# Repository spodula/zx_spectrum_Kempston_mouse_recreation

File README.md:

# zx_spectrum_Kempston_mouse_recreation
This is a copy of the classic Kempston mouse interface re-designed to use Amiga mice.
it uses all the same components, just pinout of the mouse connector differs from the classic kempston mouse.
(So in the unlikely event you have an original kempston mouse, DO NOT plug it in)
I personally use an amiga Mouse adapter I got from Ebay with an old Dell Optical mouse. This seems to work fine. 

Gerbers files are complete, and you should just be able to zip them up and send them straight to your PCB manafacturer of your choice. 

All of this was done from the Schematics available at: 
Kio at https://k1.spdns.de/Vintage/Sinclair/82/Peripherals/Mouse%20Interfaces/Kempston%20Mouse%20Interface/
My additions are:
* support for 3 button mice
* Re-arrange pinout so its compatable with the Amiga mouse. 

BUGS!
-----
Minor bug, C1 should be next to C2, and C8 should be where C1 is for decoupling!
Fortunately, as the board is overly decoupled anyway (And frankly, its doubtful if U2 needs decoupling, as its only changes its logic states a few tens of times a second at most), this isnt really an issue, HOWEVER Do make sure you dont put a 100nf as C1. This could cause bad reads from the mouse. 

Parts required: 
---------------
* 74LS191 x4
* 74LS257 x2
* 74LS138
* 74LS00
* 74LS125
* 10nf capacitor x2
* 100nf capacitors x9
* PCB mount DB9 connector.
* Edge connector x1 (If required)

Note, the jumpers J2,3,4,5 are there because i wasnt sure of the X1/X2 Y1/Y2 order. 
Now i know, you can just jumper the squared pins off (technically Pins 2/3), so the next version probably wont have them. 
(look at the terrible photos in the folder)

No licence on this board, use it, manafacture it, sell it, fart in its general direction, have fun with it..
If you do modify it, be sure to credit Kio at the above URL.

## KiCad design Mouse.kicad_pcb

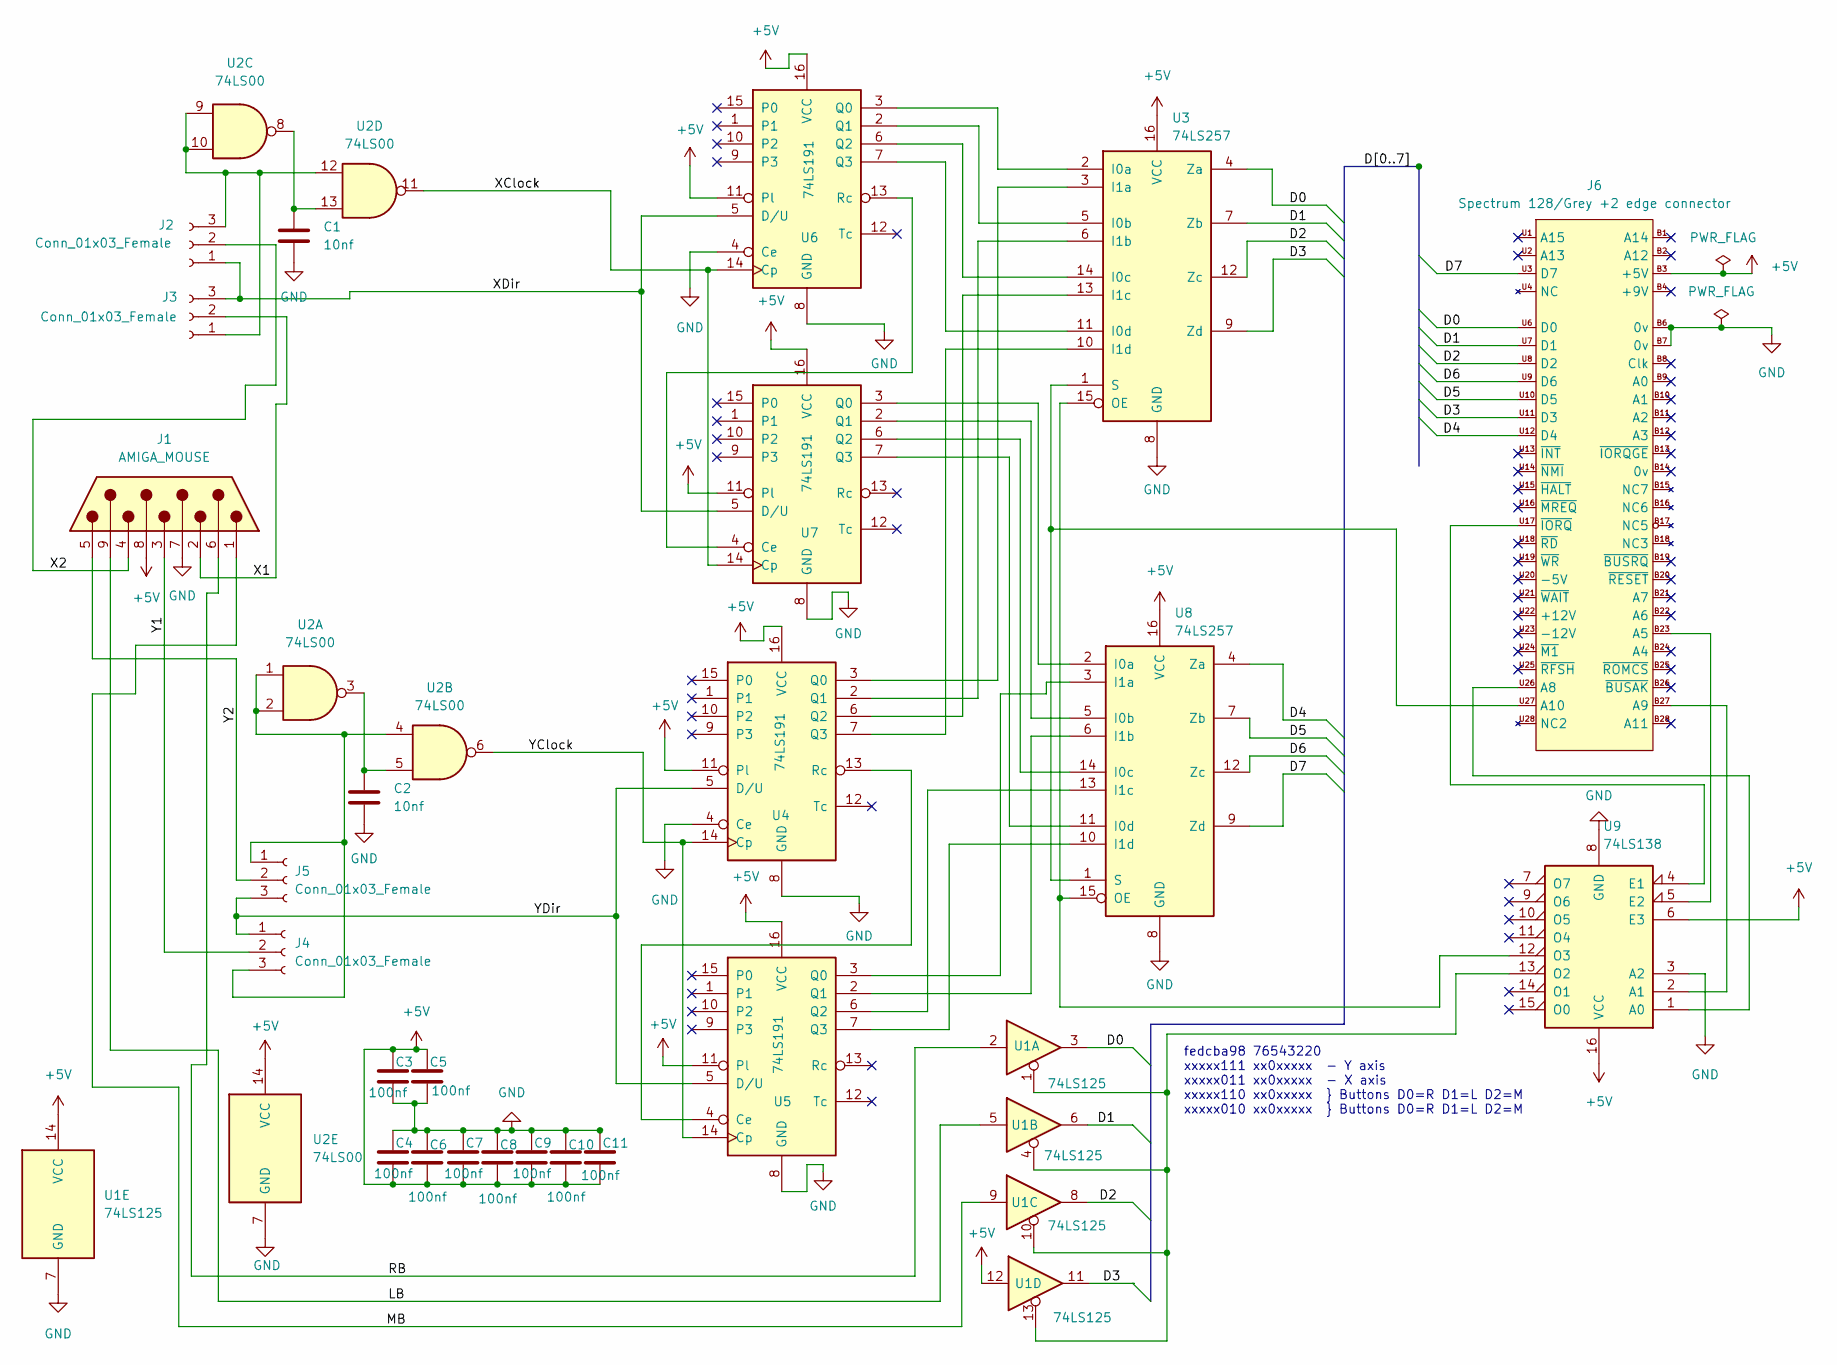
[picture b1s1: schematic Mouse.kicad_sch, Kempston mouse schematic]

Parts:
C1, C2: 10nf; C_Disc_D3.0mm_W1.6mm_P2.50mm
C3, C4, C5, C6, C7, C8, C9, C10, C11: 100nf; C_Disc_D3.0mm_W1.6mm_P2.50mm
J1: AMIGA_MOUSE; DSUB-9_Female_Horizontal_P2.77x2.84mm_EdgePinOffset4.94mm_H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
J2, J3, J4, J5: Conn_01x03_Female; PinHeader_1x03_P2.54mm_Vertical
J6: Spectrum 128/Grey +2 edge connector; Speccy_edge_External
U1: 74LS125; DIP-14_W7.62mm
U2: 74LS00; DIP-14_W7.62mm
U3, U8: 74LS257; DIP-16_W7.62mm
U4, U5, U6, U7: 74LS191; DIP-16_W7.62mm
U9: 74LS138; DIP-16_W7.62mm

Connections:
+5V: C3.1, C4.2, C5.1, C6.2, C7.2, C8.2, C9.2, C10.2, C11.2, J1.8, J6.B3 (+5V), U1.12, U1.14 (VCC), U2.14 (VCC), U3.16 (VCC), U4.11 (Pl), U4.16 (VCC), U5.11 (Pl), U5.16 (VCC), U6.11 (Pl), U6.16 (VCC), U7.11 (Pl), U7.16 (VCC), U8.16 (VCC), U9.6 (E3), U9.16 (VCC)
/D0: J6.U6 (D0), U1.3, U3.4 (Za)
/D1: J6.U7 (D1), U1.6, U3.7 (Zb)
/D2: J6.U8 (D2), U1.8, U3.12 (Zc)
/D3: J6.U11 (D3), U1.11, U3.9 (Zd)
/D4: J6.U12 (D4), U8.4 (Za)
/D5: J6.U10 (D5), U8.7 (Zb)
/D6: J6.U9 (D6), U8.12 (Zc)
/D7: J6.U3 (D7), U8.9 (Zd)
/LB: J1.9, U1.5
/MB: J1.1, U1.9
/RB: J1.6, U1.2
/X1: J1.2, J3.2
/X2: J1.4, J2.2
/XClock: U2.11, U6.14 (Cp), U7.14 (Cp)
/XDir: J2.1, J3.3, U6.5 (D/U), U7.5 (D/U)
/Y1: J1.3, J4.2
/Y2: J1.5, J5.2
/YClock: U2.6, U4.14 (Cp), U5.14 (Cp)
/YDir: J4.1, J5.3, U4.5 (D/U), U5.5 (D/U)
GND: C1.2, C2.2, C3.2, C4.1, C5.2, C6.1, C7.1, C8.1, C9.1, C10.1, C11.1, J1.7, J6.B6 (0v), J6.B7 (0v), U1.7 (GND), U2.7 (GND), U3.8 (GND), U4.4 (Ce), U4.8 (GND), U5.8 (GND), U6.4 (Ce), U6.8 (GND), U7.8 (GND), U8.8 (GND), U9.3 (A2), U9.8 (GND)
unnamed: C1.1, U2.8, U2.13
unnamed: C2.1, U2.3, U2.5
unnamed: J2.3, J3.1, U2.9, U2.10, U2.12
unnamed: J4.3, J5.1, U2.1, U2.2, U2.4
unnamed: J6.B23 (A5), U9.5 (E2)
unnamed: J6.B27 (A9), U9.2 (A1)
unnamed: J6.U17 (~IORQ), U9.4 (E1)
unnamed: J6.U26 (A8), U9.1 (A0)
unnamed: J6.U27 (A10), U3.1 (S), U8.1 (S)
unnamed: U1.1, U1.4, U1.10, U1.13, U9.13 (O2)
unnamed: U3.2 (I0a), U6.3 (Q0)
unnamed: U3.3 (I1a), U4.3 (Q0)
unnamed: U3.5 (I0b), U6.2 (Q1)
unnamed: U3.6 (I1b), U4.2 (Q1)
unnamed: U3.10 (I1d), U4.7 (Q3)
unnamed: U3.11 (I0d), U6.7 (Q3)
unnamed: U3.13 (I1c), U4.6 (Q2)
unnamed: U3.14 (I0c), U6.6 (Q2)
unnamed: U3.15 (OE), U8.15 (OE), U9.12 (O3)
unnamed: U4.13 (Rc), U5.4 (Ce)
unnamed: U5.2 (Q1), U8.6 (I1b)
unnamed: U5.3 (Q0), U8.3 (I1a)
unnamed: U5.6 (Q2), U8.13 (I1c)
unnamed: U5.7 (Q3), U8.10 (I1d)
unnamed: U6.13 (Rc), U7.4 (Ce)
unnamed: U7.2 (Q1), U8.5 (I0b)
unnamed: U7.3 (Q0), U8.2 (I0a)
unnamed: U7.6 (Q2), U8.14 (I0c)
unnamed: U7.7 (Q3), U8.11 (I0d)

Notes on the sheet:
fedcba98 76543220 xxxxx111 xx0xxxxx - Y axis xxxxx011 xx0xxxxx - X axis xxxxx110 xx0xxxxx } Buttons D0=R D1=L D2=M xxxxx010 xx0xxxxx } Buttons D0=R D1=L D2=M

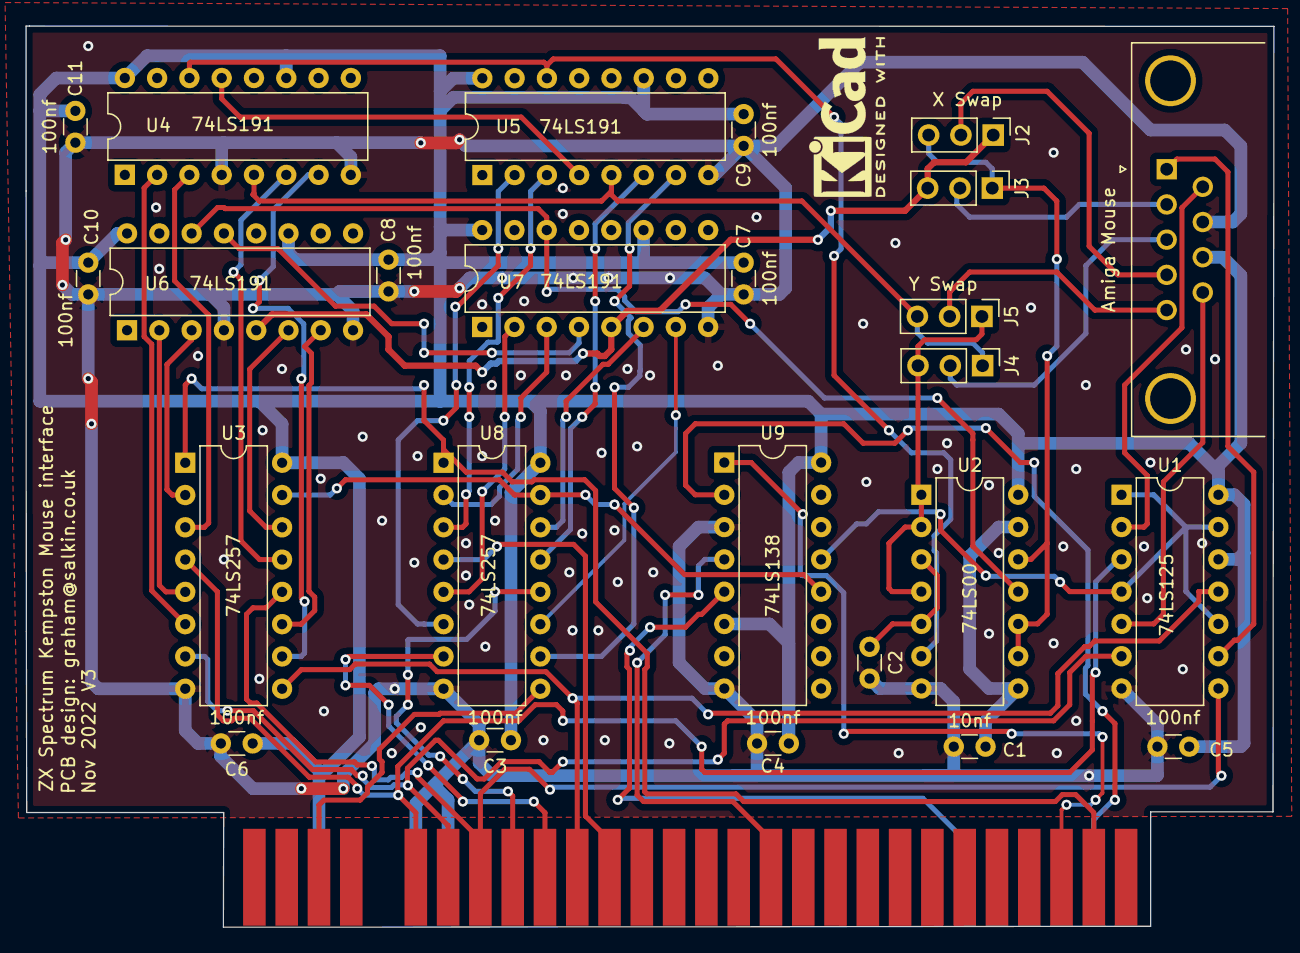
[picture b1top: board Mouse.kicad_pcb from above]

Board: 2 copper layers, 98.2 x 70.9 mm, 26 parts (0 on the bottom side), 50 nets.

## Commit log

2022-12-17 Initial login
2023-01-01 Added schematic in readable format
2023-01-02 Update README.md
    Added BUG....
2023-11-11 fixed README.md
    Fixed component name for 74ls125
